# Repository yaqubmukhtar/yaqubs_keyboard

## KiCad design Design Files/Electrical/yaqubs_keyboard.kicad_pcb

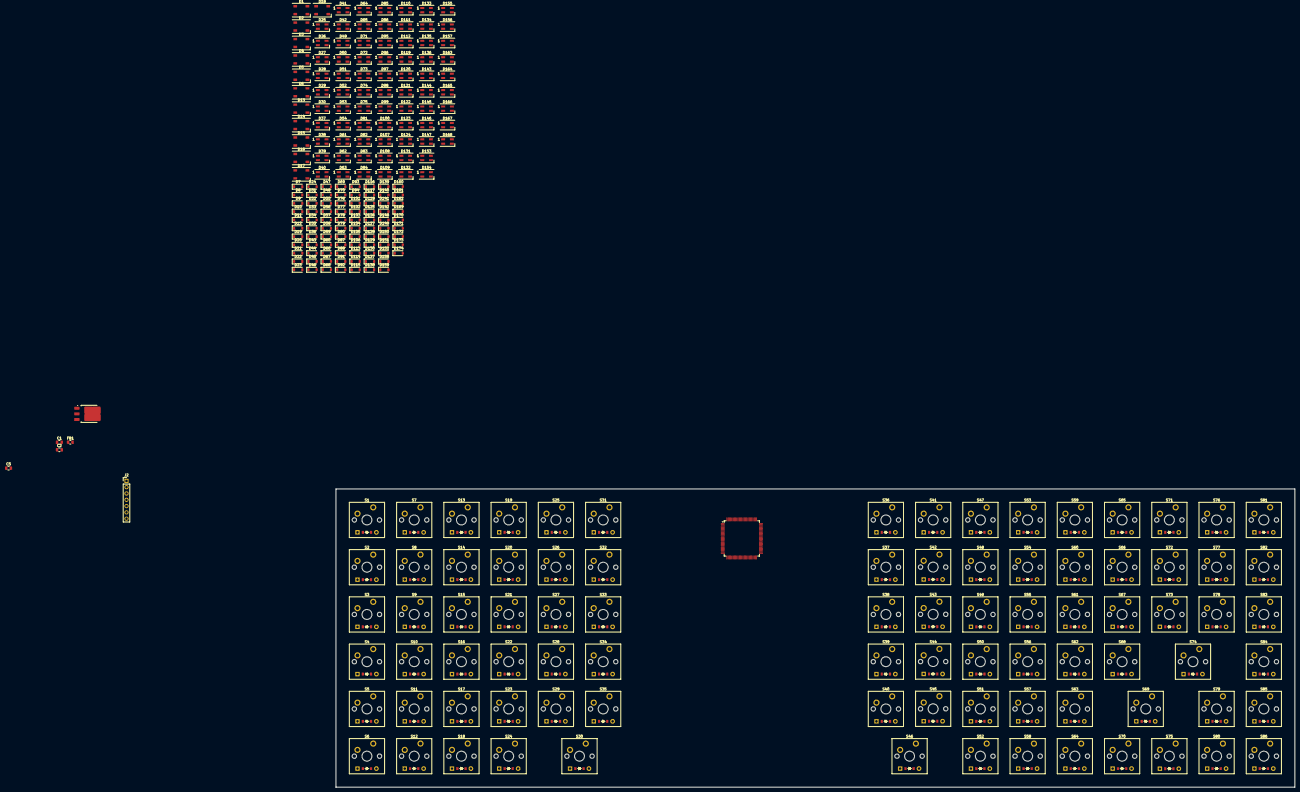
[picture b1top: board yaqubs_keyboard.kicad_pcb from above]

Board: 2 copper layers, 386.6 x 120.2 mm, 351 parts (0 on the bottom side), 181 nets, no tracks yet.

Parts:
C1, C2, C5: 1u; C_0805_2012Metric
D1, D2, D3#2, D4, D5, D6#2, D7#2, D8, D9#2, D10#2, D11, D12, D13#2, D14#2, D15#2, D16#2, D17, D18#2, D19, D20#2, D21, D22, D23, D24#2, D25#2, D26#2, D27#2, D28, D29, D30, D31#2, D32, D33, D34, D35#2, D36, D37#2, D38#2, D39#2, D40, D41#2, D42#2, D43, D44#2, D45, D46#2, D47#2, D48#2, D49, D50, D51, D52#2, D53, D54, D55#2, D56, D57#2, D58, D59#2, D60, D61, D62#2, D63#2, D64#2, D65, D66#2, D67, D68, D69#2, D70#2, D71, D72, D73#2, D74, D75, D76#2, D77#2, D78#2, D79, D80#2, D81#2, D82, D83#2, D84, D85#2, D86#2: ComboDiode
D1#2, D2#2, D3, D4#2, D5#2, D6, D13, D14, D15, D16, D17#2, D18: SK6812; LED_SK6812_PLCC4_5.0x5.0mm_P3.2mm
D7, D8#2, D9, D10, D11#2, D12#2, D19#2, D20, D21#2, D22#2, D23#2, D24, D31, D32#2, D33#2, D34#2, D35, D36#2, D43#2, D44, D45#2, D46, D47, D48, D55, D56#2, D57, D58#2, D59, D60#2, D66, D67#2, D68#2, D69, D70, D76, D77, D78, D79#2, D80, D87, D88, D91, D92, D93, D94, D101, D102, D103, D104, D105, D106, D113, D114, D115, D116, D117, D118, D125, D126, D127, D128, D129, D130, D137, D138, D139, D140, D141, D142, D148, D149, D150, D151, D152, D158, D159, D160, D161, D162, D169, D170, D171, D172, D173, D174: 1N4148W; D_SOD-123
D25, D26, D27, D28#2, D29#2, D30#2, D37, D38, D39, D40#2, D41, D42, D49#2, D50#2, D51#2, D52, D53#2, D54#2, D61#2, D62, D63, D64, D65#2, D71#2, D72#2, D73, D74#2, D75#2, D81, D82#2, D83, D84#2, D85, D86, D95, D96, D97, D98, D99, D100, D107, D108, D109, D110, D111, D112, D119, D120, D121, D122, D123, D124, D131, D132, D133, D134, D135, D136, D143, D144, D145, D146, D147, D153, D154, D155, D156, D157, D163, D164, D165, D166, D167, D168: SK6812; LED_SK6812MINI_PLCC4_3.5x3.5mm_P1.75mm
FB1: 100Ω @ 100MHz; R_0805_2012Metric
J2: OLED Interface; PinHeader_1x07_P2.54mm_Vertical
S1, S2, S3, S4, S5, S6, S7, S8, S9, S10, S11, S12, S13, S14, S15, S16, S17, S18, S19, S20, S21, S22, S23, S24, S25, S26, S27, S28, S29, S30, S31, S32, S33, S34, S35, S36, S37, S38, S39, S40, S41, S42, S43, S44, S45, S46, S47, S48, S49, S50, S51, S52, S53, S54, S55, S56, S57, S58, S59, S60, S61, S62, S63, S64, S65, S66, S67, S68, S69, S70, S71, S72, S73, S74, S75, S76, S77, S78, S79, S80, S81, S82, S83, S84, S85, S86: SW_Cherry_MX_PCB_1.00u
U1: STM32G474VETx; LQFP-100_14x14mm_P0.5mm
U2: AMS1117CD-3.3; TO-252-3_TabPin2

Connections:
+3V3: C2.1, C5.1, J2.2, U1.6 (VBAT), U1.24 (VDD), U1.37 (VDDA), U1.49 (VDD), U1.64 (VDD), U1.75 (VDD), U1.100 (VDD), U2.2 (VO)
+5V: C1.1, D1#2.3 (VDD), D2#2.3 (VDD), D3.3 (VDD), D4#2.3 (VDD), D5#2.3 (VDD), D6.3 (VDD), D13.3 (VDD), D14.3 (VDD), D15.3 (VDD), D16.3 (VDD), D17#2.3 (VDD), D18.3 (VDD), D25.3 (VDD), D26.3 (VDD), D27.3 (VDD), D28#2.3 (VDD), D29#2.3 (VDD), D30#2.3 (VDD), D37.3 (VDD), D38.3 (VDD), D39.3 (VDD), D40#2.3 (VDD), D41.3 (VDD), D42.3 (VDD), D49#2.3 (VDD), D50#2.3 (VDD), D51#2.3 (VDD), D52.3 (VDD), D53#2.3 (VDD), D54#2.3 (VDD), D61#2.3 (VDD), D62.3 (VDD), D63.3 (VDD), D64.3 (VDD), D65#2.3 (VDD), D71#2.3 (VDD), D72#2.3 (VDD), D73.3 (VDD), D74#2.3 (VDD), D75#2.3 (VDD), D81.3 (VDD), D82#2.3 (VDD), D83.3 (VDD), D84#2.3 (VDD), D85.3 (VDD), D86.3 (VDD), D95.3 (VDD), D96.3 (VDD), D97.3 (VDD), D98.3 (VDD), D99.3 (VDD), D100.3 (VDD), D107.3 (VDD), D108.3 (VDD), D109.3 (VDD), D110.3 (VDD), D111.3 (VDD), D112.3 (VDD), D119.3 (VDD), D120.3 (VDD), D121.3 (VDD), D122.3 (VDD), D123.3 (VDD), D124.3 (VDD), D131.3 (VDD), D132.3 (VDD), D133.3 (VDD), D134.3 (VDD), D135.3 (VDD), D136.3 (VDD), D143.3 (VDD), D144.3 (VDD), D145.3 (VDD), D146.3 (VDD), D147.3 (VDD), D153.3 (VDD), D154.3 (VDD), D155.3 (VDD), D156.3 (VDD), D157.3 (VDD), D163.3 (VDD), D164.3 (VDD), D165.3 (VDD), D166.3 (VDD), D167.3 (VDD), D168.3 (VDD), U2.3 (VI)
GND: C1.2, C2.2, C5.2, D1#2.1 (VSS), D2#2.1 (VSS), D3.1 (VSS), D4#2.1 (VSS), D5#2.1 (VSS), D6.1 (VSS), D13.1 (VSS), D14.1 (VSS), D15.1 (VSS), D16.1 (VSS), D17#2.1 (VSS), D18.1 (VSS), D25.1 (VSS), D26.1 (VSS), D27.1 (VSS), D28#2.1 (VSS), D29#2.1 (VSS), D30#2.1 (VSS), D37.1 (VSS), D38.1 (VSS), D39.1 (VSS), D40#2.1 (VSS), D41.1 (VSS), D42.1 (VSS), D49#2.1 (VSS), D50#2.1 (VSS), D51#2.1 (VSS), D52.1 (VSS), D53#2.1 (VSS), D54#2.1 (VSS), D61#2.1 (VSS), D62.1 (VSS), D63.1 (VSS), D64.1 (VSS), D65#2.1 (VSS), D71#2.1 (VSS), D72#2.1 (VSS), D73.1 (VSS), D74#2.1 (VSS), D75#2.1 (VSS), D81.1 (VSS), D82#2.1 (VSS), D83.1 (VSS), D84#2.1 (VSS), D85.1 (VSS), D86.1 (VSS), D95.1 (VSS), D96.1 (VSS), D97.1 (VSS), D98.1 (VSS), D99.1 (VSS), D100.1 (VSS), D107.1 (VSS), D108.1 (VSS), D109.1 (VSS), D110.1 (VSS), D111.1 (VSS), D112.1 (VSS), D119.1 (VSS), D120.1 (VSS), D121.1 (VSS), D122.1 (VSS), D123.1 (VSS), D124.1 (VSS), D131.1 (VSS), D132.1 (VSS), D133.1 (VSS), D134.1 (VSS), D135.1 (VSS), D136.1 (VSS), D143.1 (VSS), D144.1 (VSS), D145.1 (VSS), D146.1 (VSS), D147.1 (VSS), D153.1 (VSS), D154.1 (VSS), D155.1 (VSS), D156.1 (VSS), D157.1 (VSS), D163.1 (VSS), D164.1 (VSS), D165.1 (VSS), D166.1 (VSS), D167.1 (VSS), D168.1 (VSS), J2.1, U1.23 (VSS), U1.35 (VSSA), U1.48 (VSS), U1.63 (VSS), U1.74 (VSS), U1.99 (VSS), U2.1 (GND)
MOSI: J2.4, U1.22 (PA2)
unnamed: D1#2.4 (DOUT), D13.2 (DIN)
unnamed: D13.4 (DOUT), D25.2 (DIN)
unnamed: D2#2.4 (DOUT), D14.2 (DIN)
unnamed: D14.4 (DOUT), D26.2 (DIN)
unnamed: D3.4 (DOUT), D15.2 (DIN)
unnamed: D15.4 (DOUT), D27.2 (DIN)
unnamed: D4#2.4 (DOUT), D16.2 (DIN)
unnamed: D16.4 (DOUT), D28#2.2 (DIN)
unnamed: D5#2.4 (DOUT), D17#2.2 (DIN)
unnamed: D17#2.4 (DOUT), D29#2.2 (DIN)
unnamed: D6.4 (DOUT), D18.2 (DIN)
unnamed: D18.4 (DOUT), D30#2.2 (DIN)
unnamed: D25.4 (DOUT), D37.2 (DIN)
unnamed: D26.4 (DOUT), D38.2 (DIN)
unnamed: D27.4 (DOUT), D39.2 (DIN)
unnamed: D28#2.4 (DOUT), D40#2.2 (DIN)
unnamed: D29#2.4 (DOUT), D41.2 (DIN)
unnamed: D30#2.4 (DOUT), D42.2 (DIN)
unnamed: D37.4 (DOUT), D49#2.2 (DIN)
unnamed: D38.4 (DOUT), D50#2.2 (DIN)
unnamed: D39.4 (DOUT), D51#2.2 (DIN)
unnamed: D40#2.4 (DOUT), D52.2 (DIN)
unnamed: D41.4 (DOUT), D53#2.2 (DIN)
unnamed: D42.4 (DOUT), D54#2.2 (DIN)
unnamed: D49#2.4 (DOUT), D61#2.2 (DIN)
unnamed: D50#2.4 (DOUT), D62.2 (DIN)
unnamed: D51#2.4 (DOUT), D63.2 (DIN)
unnamed: D52.4 (DOUT), D64.2 (DIN)
unnamed: D53#2.4 (DOUT), D65#2.2 (DIN)
unnamed: D54#2.4 (DOUT), D86.2 (DIN)
unnamed: D61#2.4 (DOUT), D71#2.2 (DIN)
unnamed: D62.4 (DOUT), D72#2.2 (DIN)
unnamed: D63.4 (DOUT), D73.2 (DIN)
unnamed: D64.4 (DOUT), D74#2.2 (DIN)
unnamed: D65#2.4 (DOUT), D75#2.2 (DIN)
unnamed: D71#2.4 (DOUT), D81.2 (DIN)
unnamed: D72#2.4 (DOUT), D82#2.2 (DIN)
unnamed: D73.4 (DOUT), D83.2 (DIN)
unnamed: D74#2.4 (DOUT), D84#2.2 (DIN)
unnamed: D75#2.4 (DOUT), D85.2 (DIN)
unnamed: D81.4 (DOUT), D95.2 (DIN)
unnamed: D82#2.4 (DOUT), D96.2 (DIN)
unnamed: D83.4 (DOUT), D97.2 (DIN)
unnamed: D84#2.4 (DOUT), D98.2 (DIN)
unnamed: D85.4 (DOUT), D99.2 (DIN)
unnamed: D86.4 (DOUT), D100.2 (DIN)
unnamed: D100.4 (DOUT), D112.2 (DIN)
unnamed: D95.4 (DOUT), D107.2 (DIN)
unnamed: D107.4 (DOUT), D119.2 (DIN)
unnamed: D96.4 (DOUT), D108.2 (DIN)
unnamed: D108.4 (DOUT), D120.2 (DIN)
unnamed: D97.4 (DOUT), D109.2 (DIN)
unnamed: D109.4 (DOUT), D121.2 (DIN)
unnamed: D98.4 (DOUT), D110.2 (DIN)
unnamed: D110.4 (DOUT), D122.2 (DIN)
unnamed: D99.4 (DOUT), D111.2 (DIN)
unnamed: D111.4 (DOUT), D123.2 (DIN)
unnamed: D112.4 (DOUT), D124.2 (DIN)
unnamed: D119.4 (DOUT), D131.2 (DIN)
unnamed: D120.4 (DOUT), D132.2 (DIN)
unnamed: D121.4 (DOUT), D133.2 (DIN)
unnamed: D122.4 (DOUT), D134.2 (DIN)
unnamed: D123.4 (DOUT), D135.2 (DIN)
unnamed: D124.4 (DOUT), D136.2 (DIN)
unnamed: D131.4 (DOUT), D143.2 (DIN)
unnamed: D132.4 (DOUT), D144.2 (DIN)
unnamed: D133.4 (DOUT), D145.2 (DIN)
unnamed: D134.4 (DOUT), D146.2 (DIN)
unnamed: D135.4 (DOUT), D147.2 (DIN)
unnamed: D136.4 (DOUT), D168.2 (DIN)
unnamed: D143.4 (DOUT), D153.2 (DIN)
unnamed: D144.4 (DOUT), D154.2 (DIN)
unnamed: D145.4 (DOUT), D155.2 (DIN)
unnamed: D146.4 (DOUT), D156.2 (DIN)
unnamed: D147.4 (DOUT), D157.2 (DIN)
unnamed: D153.4 (DOUT), D163.2 (DIN)
unnamed: D154.4 (DOUT), D164.2 (DIN)
unnamed: D155.4 (DOUT), D165.2 (DIN)
unnamed: D156.4 (DOUT), D166.2 (DIN)
unnamed: D157.4 (DOUT), D167.2 (DIN)
unnamed: D2#2.2 (DIN), D163.4 (DOUT)
unnamed: D3.2 (DIN), D164.4 (DOUT)
unnamed: D4#2.2 (DIN), D165.4 (DOUT)
unnamed: D5#2.2 (DIN), D166.4 (DOUT)
unnamed: D6.2 (DIN), D167.4 (DOUT)
ROW0: D7.1 (K), D19#2.1 (K), D31.1 (K), D43#2.1 (K), D55.1 (K), D66.1 (K), D76.1 (K), D87.1 (K), D101.1 (K), D113.1 (K), D125.1 (K), D137.1 (K), D148.1 (K), D158.1 (K), D169.1 (K)
ROW1: D8#2.1 (K), D20.1 (K), D32#2.1 (K), D44.1 (K), D56#2.1 (K), D67#2.1 (K), D77.1 (K), D88.1 (K), D102.1 (K), D114.1 (K), D126.1 (K), D138.1 (K), D149.1 (K), D159.1 (K), D170.1 (K)
ROW2: D9.1 (K), D21#2.1 (K), D33#2.1 (K), D45#2.1 (K), D57.1 (K), D68#2.1 (K), D78.1 (K), D91.1 (K), D103.1 (K), D115.1 (K), D127.1 (K), D139.1 (K), D150.1 (K), D160.1 (K), D171.1 (K)
ROW3: D10.1 (K), D22#2.1 (K), D34#2.1 (K), D46.1 (K), D58#2.1 (K), D69.1 (K), D79#2.1 (K), D92.1 (K), D104.1 (K), D116.1 (K), D128.1 (K), D140.1 (K), D151.1 (K), D161.1 (K), D172.1 (K)
ROW4: D11#2.1 (K), D23#2.1 (K), D35.1 (K), D47.1 (K), D59.1 (K), D70.1 (K), D80.1 (K), D93.1 (K), D105.1 (K), D117.1 (K), D129.1 (K), D141.1 (K), D152.1 (K), D162.1 (K), D173.1 (K)
ROW5: D12#2.1 (K), D24.1 (K), D36#2.1 (K), D48.1 (K), D60#2.1 (K), D94.1 (K), D106.1 (K), D118.1 (K), D130.1 (K), D142.1 (K), D174.1 (K)
SCLK: J2.3, U1.21 (PA1)
col1_bottom: D70#2.2, S70.2
col1_func: D71.2, S71.2
col1_num: D72.2, S72.2
col1_space: D74.2, S74.2
col1_top: D73#2.2, S73.2
col2_bottom: D79.2, S79.2
col2_func: D76#2.2, S76.2
col2_home: D75.2, S75.2
col2_num: D77#2.2, S77.2
col2_space: D80#2.2, S80.2
col2_top: D78#2.2, S78.2
col3_bottom: D85#2.2, S85.2
col3_func: D81#2.2, S81.2
col3_home: D84.2, S84.2
col3_num: D82.2, S82.2
col3_space: D86#2.2, S86.2
col3_top: D83#2.2, S83.2
index1_bottom: D23.2, S23.2
index1_func: D19.2, S19.2
index1_home: D22.2, S22.2
index1_num: D20#2.2, S20.2
index1_space: D24#2.2, S24.2
index1_top: D21.2, S21.2
index2_bottom: D51.2, S51.2
index2_func: D47#2.2, S47.2
index2_home: D50.2, S50.2
index2_num: D48#2.2, S48.2
index2_space: D52#2.2, S52.2
index2_top: D49.2, S49.2
inner1_bottom: D29.2, S29.2
inner1_func: D25#2.2, S25.2
inner1_home: D28.2, S28.2
inner1_num: D26#2.2, S26.2
inner1_top: D27#2.2, S27.2
inner2_bottom: D46#2.2, S46.2
inner2_func: D42#2.2, S42.2
inner2_home: D45.2, S45.2
inner2_num: D43.2, S43.2
inner2_top: D44#2.2, S44.2
middle1_bottom: D17.2, S17.2
middle1_func: D13#2.2, S13.2
middle1_home: D16#2.2, S16.2
middle1_num: D14#2.2, S14.2
middle1_space: D18#2.2, S18.2
middle1_top: D15#2.2, S15.2
middle2_bottom: D57#2.2, S57.2
middle2_func: D53.2, S53.2
middle2_home: D56.2, S56.2
middle2_num: D54.2, S54.2
middle2_space: D58.2, S58.2
middle2_top: D55#2.2, S55.2
pinky1_bottom: D5.2, S5.2
pinky1_func: D1.2, S1.2
pinky1_home: D4.2, S4.2
pinky1_num: D2.2, S2.2
pinky1_space: D6#2.2, S6.2
pinky1_top: D3#2.2, S3.2
pinky2_func: D65.2, S65.2
pinky2_home: D68.2, S68.2
pinky2_num: D66#2.2, S66.2
pinky2_space: D69#2.2, S69.2
pinky2_top: D67.2, S67.2
ring1_bottom: D11.2, S11.2
ring1_func: D7#2.2, S7.2
ring1_home: D10#2.2, S10.2
ring1_num: D8.2, S8.2
ring1_space: D12.2, S12.2
ring1_top: D9#2.2, S9.2
ring2_bottom: D63#2.2, S63.2
ring2_func: D59#2.2, S59.2
ring2_home: D62#2.2, S62.2
ring2_num: D60.2, S60.2
ring2_space: D64#2.2, S64.2
ring2_top: D61.2, S61.2
space_default: D30.2, D41#2.2, S30.2, S41.2
thumb1_bottom: D35#2.2, S35.2
thumb1_func: D31#2.2, S31.2
thumb1_home: D34.2, S34.2
thumb1_num: D32.2, S32.2
thumb1_top: D33.2, S33.2
thumb2_bottom: D40.2, S40.2
thumb2_func: D36.2, S36.2
thumb2_home: D39#2.2, S39.2
thumb2_num: D37#2.2, S37.2
thumb2_top: D38#2.2, S38.2

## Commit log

2024-11-17 init commit
2024-12-27 auto-generated case, pcb with mounting holes.
